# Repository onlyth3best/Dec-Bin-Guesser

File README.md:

# Dec-Bin-Guesser
a decimal/binary guessing game on a PCB!
(built with help from https://pathfinder.hackclub.com/)

<br/> About the folders: /code has all the code, /prod has all the production files!

<br/> (An image of the schematics!) <br/>

<br/> (pcb editor above, routing is a _little_ messy…)

<br/> note: PCB models are in pcb/kicad! other 3D models that were used were not sourced by me :)
<br/>
<br/>_20/04/2026:_
<br/> For now, the code is only for the decimal system guessing, as I haven't had time to test it out with the actual PCB yet. This is the idea, though:
<br/>- It'll begin with a level select, where you press either the left button (LB) or the right button (RB) to select decimal/binary guessing respectively.
<br/>- (Once you have selected a level, the PCB will generate a random number…)
<br/>- If the level is decimal guessing, the LB will add 10s while the RB will add 1s. The binary guessing is simmilar, except the LB will add 0s to a string instead.
<br/>- The centre button confirms your guess…
<br/>- if it's too large, the LED on the right will light up. If it's too small, the LED on the left will light up. Just right, and the centre will light up & the buzzer will sound!
<br/>- (_an alternative idea: another level, where the buzzer signals a timer… figure out the value before the time runs out!_)

<br/> in terms of code, I haven't fully done the firmware as I don't have the actual thing yet, but here's a guide for setting up the XIAO_RP2040 with Arduino: https://wiki.seeedstudio.com/XIAO-RP2040-with-Arduino/
<br/> The firmware I've added is in progress as of now (21/04/26) and I will add setup steps in the future, when I have the physical PCB itself.
<br/>
<br/>Setup Guide (to be edited):
<br/>  -Connect to the XIAO, using the Arduino IDE
<br/>  -This link might help: https://wiki.seeedstudio.com/XIAO-RP2040-with-Arduino/
<br/>  -The code should work… once I've finished polishing it (not completely done as of now…)

<br/> Wiring:
<br/> button1 = D0
<br/> button2 = D1
<br/> button3 = D2
<br/> LED1 = D3
<br/> LED2 = D4
<br/> LED3 = D5
<br/> buzzer1 = D6 (P0_D6_TX)

<br/>
<br/>Assembly instructions, for now:
<br/>~ Solder these things onto the PCB, according to the schematics:
<br/>~ - XIAO_RP_2040
<br/>~ - three LEDs
<br/>~ - three resistors
<br/>~ - three buttons
<br/>~ - buzzer
<br/>~ After this, connect the board to the power, this link could help: https://wiki.seeedstudio.com/XIAO-RP2040-with-Arduino/
<br/>also Flash instructions:
<br/> - install ArduinoIDE, https://docs.arduino.cc/software/ide/
<br/> - add the support for the RP2040 (Preferences > Additional Board Manager URLs > "https://github.com/earlephilhower/arduino-pico/releases/download/global/package_rp2040_index.json")
<br/> - connect the XIAO RP_2040 via USB
<br/> - upload the code from this repo in /firmware!

PCB BOM:
<br/>
<br/>
<br/>

| Reference  | Qty | Value | approx price in USD | links I found|
| ------------- | ------------- | ------------- | ------------- | ------------- |
| U1  | 1 | Seeed Studio XIAO RP2040 | $ 3.9 | [link](https://www.seeedstudio.com/XIAO-RP2040-v1-0-p-5026.html?srsltid=AfmBOor69gTiD1i0IEN-NgJbt-CYkVZTgTP96P1gkFrOACfPGnEJtVJv) / microcontroller board |
| D1, D2, D3  | 3 | LED / L08R5000Q1 | $ 0.1 | https://jlcpcb.com/partdetail/JLCPCBAssembly-LED_NCD0805C1/C9900035298 |
| R1, R2, R3  | 3 | resistor | $ 0.01 | https://jlcpcb.com/partdetail/TyoHM-RMC_0603_10K_JN/C5362358 |
| SW1, Sw2, SW3  | 3 | Button/Switch | $ 0.5 | [https://jlcpcb.com/partdetail/ESwitch-TL3301AF160QG/C273519 |
| BZ1  | 1 | Buzzer | % 0.5 | https://jlcpcb.com/partdetail/Jiangsu_HuanengElec-HND2310B/C2877 |

<br/> planning to source from JLCPCB (apologies if the BOM is wrong, I'm new to this)

<br/>
<br/>Why did I build it? Well, I don't have many pocket-games– games I can play while travelling, etc. Plus, I haven't made many hardware projects in the past, so this is sort of my first attempt at designing a PCB, which I'd say was my main motivation.

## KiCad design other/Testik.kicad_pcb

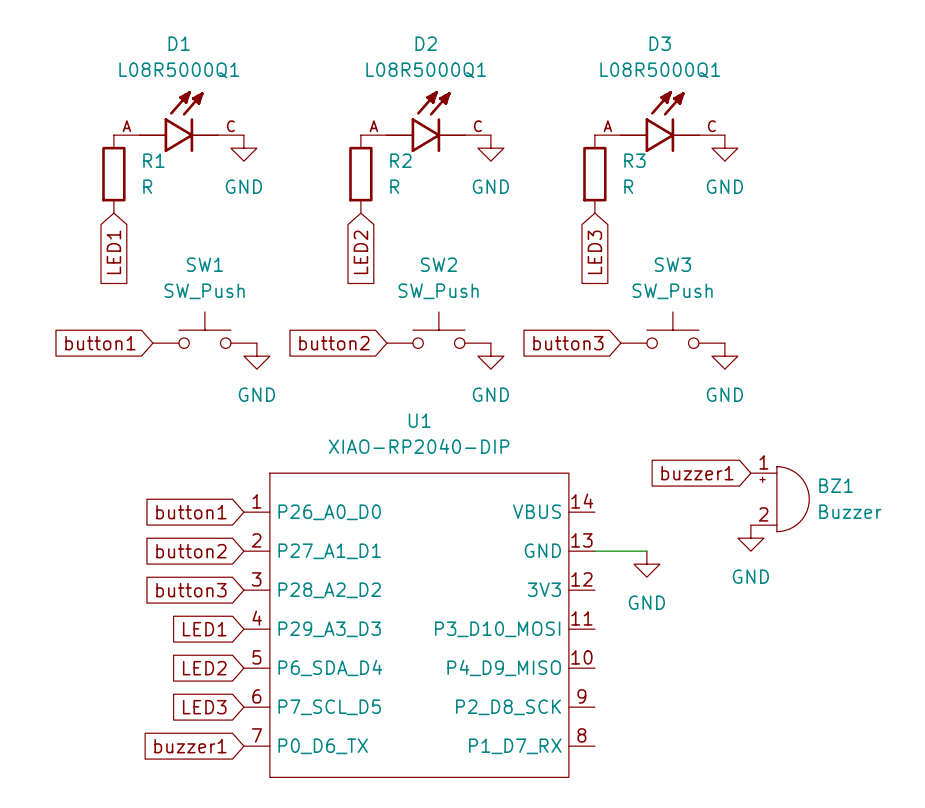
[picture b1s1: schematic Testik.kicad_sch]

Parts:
BZ1: Buzzer; Buzzer_12x9.5RM7.6
D1, D2, D3: L08R5000Q1; LEDRD254W57D500H1070; PARTREV NA
R1, R2, R3: R; R_Axial_DIN0204_L3.6mm_D1.6mm_P5.08mm_Horizontal
SW1, SW2, SW3: SW_Push; SW_Cherry_MX_1.00u_PCB
U1: XIAO-RP2040-DIP

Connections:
GND: BZ1.2 (-), D1.C, D2.C, D3.C, SW1.2, SW2.2, SW3.2, U1.13 (GND)
LED1: R1.2, U1.4 (P29_A3_D3)
LED2: R2.2, U1.5 (P6_SDA_D4)
LED3: R3.2, U1.6 (P7_SCL_D5)
unnamed: D1.A, R1.1
unnamed: D2.A, R2.1
unnamed: D3.A, R3.1
button1: SW1.1, U1.1 (P26_A0_D0)
button2: SW2.1, U1.2 (P27_A1_D1)
button3: SW3.1, U1.3 (P28_A2_D2)
buzzer1: BZ1.1 (+), U1.7 (P0_D6_TX)

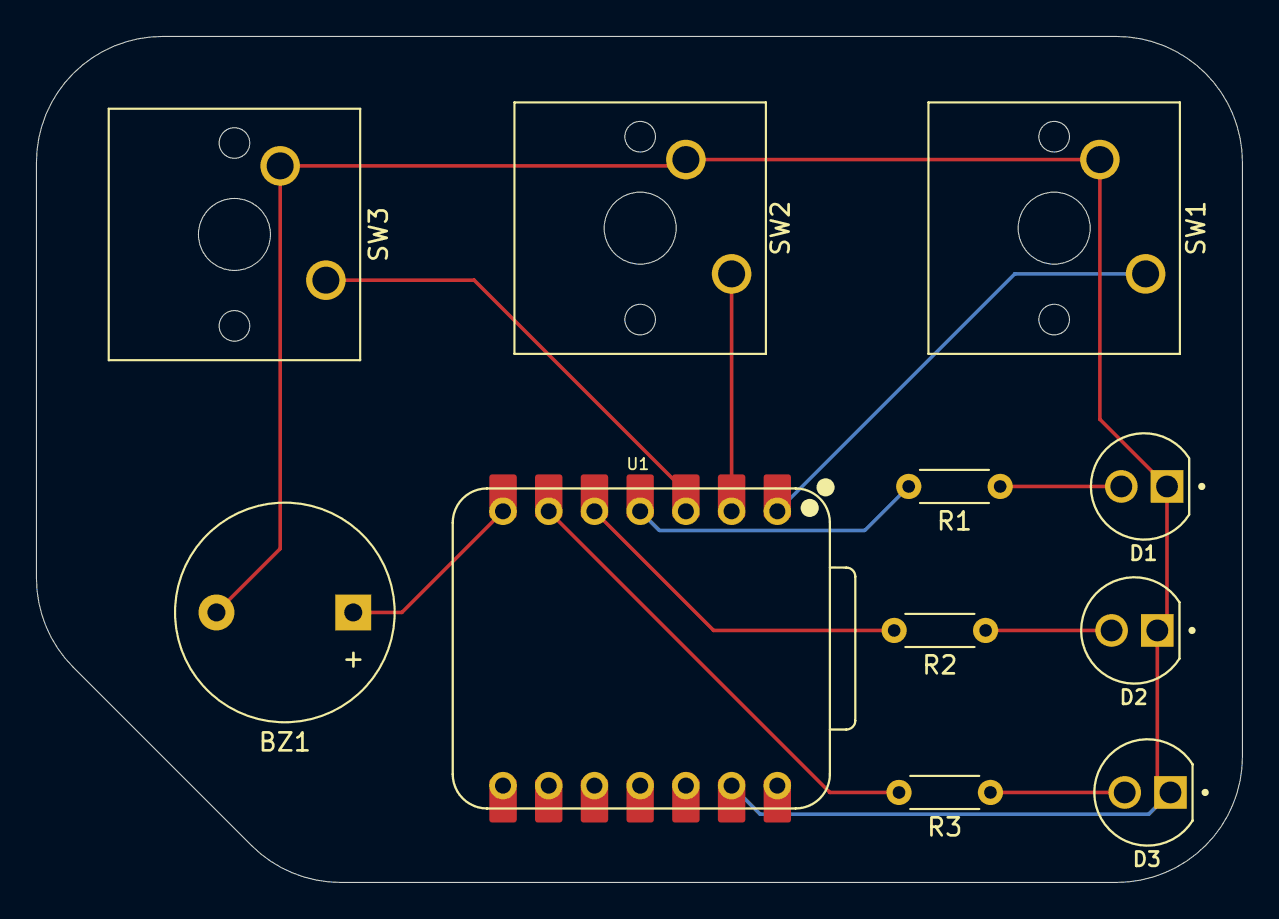
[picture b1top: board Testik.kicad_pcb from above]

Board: 2 copper layers, 67.0 x 47.0 mm, 11 parts (0 on the bottom side), 11 nets.

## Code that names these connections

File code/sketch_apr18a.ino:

/*

&& and
|| or

button1 = D0
button2 = D1
button3 = D2
LED1 = D3
LED2 = D4
LED3 = D5
buzzer1 = D6 (P0_D6_TX)

int len = 0;
int pGBdec = 0;
int base = 1;
*/
int playerGuess = 0;
int theRandomNumber = random(1, 100);


int BUT1 = D0;
int BUT2 = D1;
int BUT3 = D2;

int LED1 = D3;
int LED2 = D4;
int LED3 = D5;
int BUZZ = D6;

/* - - - - - - - */

void setup() {
  pinMode(BUT1, INPUT_PULLUP);
  pinMode(BUT2, INPUT_PULLUP);
  pinMode(BUT3, INPUT_PULLUP);

  pinMode(LED1, OUTPUT);
  pinMode(LED2, OUTPUT);
  pinMode(LED3, OUTPUT);

  pinMode(BUZZ, OUTPUT);

  Serial.begin(9600);
  long startTime = millis();
}

/* - - - - - - - */



void loop() {
  /* example */
  long but1time;
  long but2time;
  long but3time = 0;


  if (digitalRead(BUT1) == HIGH) {
    playerGuess += 10;
    Serial.println(playerGuess); /*so i can check stuff*/
    delay(200);
  }
  if (digitalRead(BUT3) == HIGH) {
    playerGuess += 1;
    Serial.println(playerGuess);
    delay(200);
  }


  if (digitalRead(BUT2) == HIGH) {  
    if (playerGuess == theRandomNumber) {
      digitalWrite(LED2, LOW);
      delay(500);
      digitalWrite(LED2, HIGH);
      delay(500);

      playerGuess = 0; /*to reset*/
      theRandomNumber = random(1, 100);
    }

    else if (playerGuess > theRandomNumber) {
      digitalWrite(LED3, HIGH);
      delay(1000);
      digitalWrite(LED3, LOW);
    }

    else { /*less than, as well as some other cases I suppose? errors, etc*/
      digitalWrite(LED1, HIGH);
      delay(1000);
      digitalWrite(LED1, LOW);
    }
  }
} /*end loop*/







/*
    for (int i = len - 1; i >= 0; i--) {
      if (playerGuessBin[i] == '1') {
        pGBdec += base;
      }
      base = base * 2;
    }
*/

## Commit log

2026-04-20 Create test
2026-04-20 Create Production!
2026-04-20 Create Code!
2026-04-20 Create placeholder
2026-04-21 Create stuff
2026-05-07 Create t
2026-05-16 Rename debcin.pdf to decbinZinePDF.pdf
